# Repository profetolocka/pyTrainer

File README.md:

# pyTrainer

**pyTrainer** es un completo kit educativo diseñado para aquellos que desean introducirse en el apasionante mundo del aprendizaje de Micropython.

Ha sido creado teniendo como objetivo la sencillez y la economía, ya que puede ser replicado y construido por estudiantes o aficionados empleando técnicas caseras.

Está formado por una placa principal llamada **pyTrainer BASIC**, módulos de sensores y actuadores para interactuar con el mundo real y piezas impresas en 3D para montar las placas y crear distintas estructuras.

Este conjunto de elementos permite realizar una gran cantidad de experiencias y prácticas para aprender a programar en Micropython de una forma sencilla y divertida.<br>

## Características

### Sencillez
La placa cuenta con los elementos necesarios para practicar y aprender Micropython sin necesidad de complejas configuraciones. Enchufala y comienza a usarla!

### Potencia
Basada en la D1 Mini de Wemos, cuenta con un módulo ESP8266 capaz de realizar múltiples operaciones y conectarse a Internet a través del Wifi incluido.

### Ampliable
La pyTrainer admite la conexión de distintos módulos que amplian sus capacidades: leds RGB, pulsadores, interruptores, sensores de luz y temperatura, relés son solo algunos de ellos.
Además, el módulo D1 mini acepta distintos shields que se montan sobre la placa, como un display OLED, un sensor de temperatura o una placa de prototipos.

### Hardware y software libre
¿Quieres fabricar tu propia PyTrainer? El diseño es Open Hardware, así que puedes descargar los archivos necesarios para fabricar tu propia placa y modificarla a tu gusto.
 
## Especificaciones
* CPU: Wemos D1 mini
* Salidas digitales: Tres. Cada salida además cuenta con un led testigo.
* Entradas digitales: Tres.
* Pulsadores incorporados: Dos teclas tipo touch de uso múltiple.
* Entradas analógicas: Una con un rango de 0 a 5V.
* Otros: Zumbador activo (Buzzer).
* Ampliación: Dos conectores I2C.

[Toda la información en la Wiki](https://github.com/profetolocka/pyTrainer/wiki)

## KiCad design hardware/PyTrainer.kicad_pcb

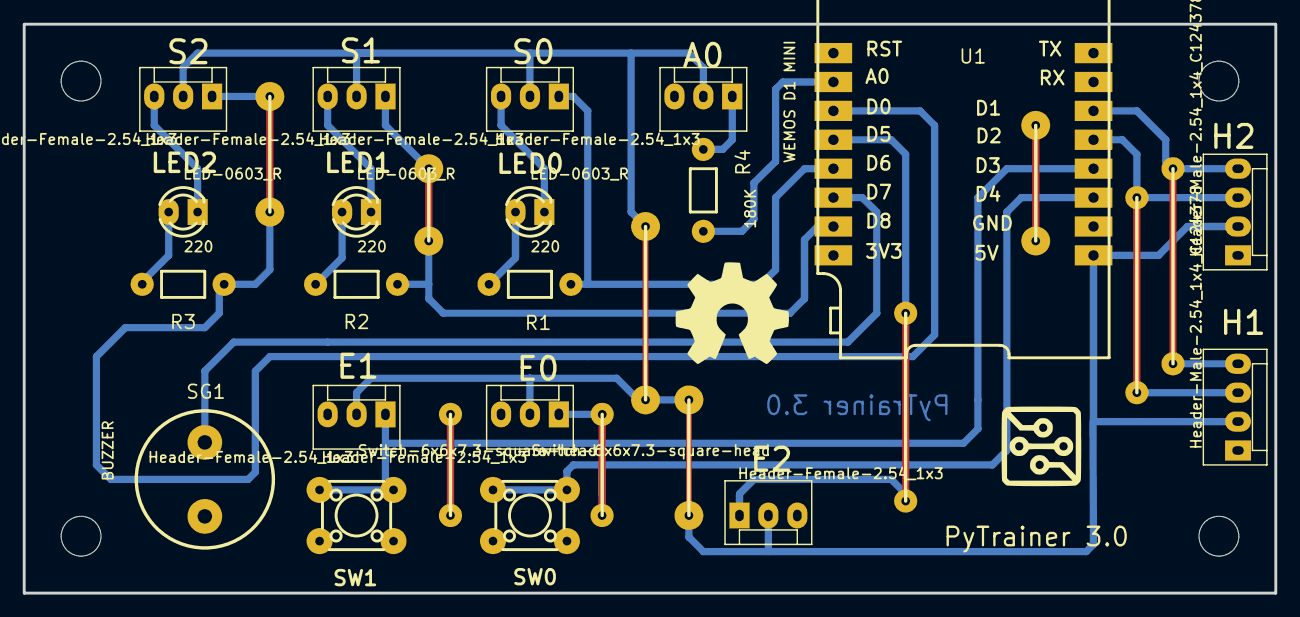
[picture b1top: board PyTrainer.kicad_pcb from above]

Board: 2 copper layers, 110.0 x 50.0 mm, 44 parts (0 on the bottom side), 16 nets.

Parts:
A0: Header-Female-2.54_1x3; MOLEX-1X3
E0, E1, E2: Header-Female-2.54_1x3; MOLEX-1X3
H1, H2: Header-Male-2.54_1x4_C124378; MOLEX-1X4
Hole_gge2783: Hole_gge2783
Hole_gge2788: Hole_gge2788
Hole_gge3649: Hole_gge3649
Hole_gge3664: Hole_gge3664
LED0, LED1, LED2: LED-0603_R; LED-TH_BD3.0-P2.54-FD
Pad_gge6454: Pad_gge6454
Pad_gge6466: Pad_gge6466
Pad_gge6478: Pad_gge6478
Pad_gge6490: Pad_gge6490
Pad_gge6502: Pad_gge6502
Pad_gge6514: Pad_gge6514
Pad_gge6526: Pad_gge6526
Pad_gge6538: Pad_gge6538
Pad_gge6550: Pad_gge6550
Pad_gge6562: Pad_gge6562
Pad_gge6574: Pad_gge6574
Pad_gge6586: Pad_gge6586
Pad_gge6598: Pad_gge6598
Pad_gge6610: Pad_gge6610
Pad_gge6622: Pad_gge6622
Pad_gge6634: Pad_gge6634
Pad_gge6655: Pad_gge6655
Pad_gge6667: Pad_gge6667
Pad_gge6679: Pad_gge6679
Pad_gge6691: Pad_gge6691
R1, R2, R3: 220; RD-3.2X1.8-1/8W
R4: 180K; RD-3.2X1.8-1/8W
S0, S1, S2: Header-Female-2.54_1x3; MOLEX-1X3
SG1: BUZZER; BUZZER-12MM-NS
SW0, SW1: Switch-6x6x7.3-square-head; SW-TH_4P-L6.0-W6.0-P4.50-LS6.5
U1: WEMOS D1 MINI

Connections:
+5V: A0.2, E0.2, E1.2, E2.2, H1.2, H2.2, S0.2, S1.2, S2.2, U1.1
A0: R4.2, U1.10
BUZZER: SG1.+, U1.14
GND: A0.3, E0.3, E1.3, E2.3, H1.1, H2.1, LED0.2, LED1.2, LED2.2, S0.3, S1.3, S2.3, SG1.-, SW0.3, SW0.4, SW1.3, SW1.4, U1.2
IN0: E1.1, SW1.1, SW1.2, U1.4
IN1: E0.1, SW0.1, SW0.2, U1.3
IN2: E2.1, U1.12
OUT0: R1.2, S0.1, U1.13
OUT1: R2.2, S1.1, U1.15
OUT2: R3.2, S2.1, U1.11
R1_1: LED0.1, R1.1
R2_1: LED1.1, R2.1
R3_1: LED2.1, R3.1
R4_1: A0.1, R4.1
SCL: H1.4, H2.4, U1.6
SDA: H1.3, H2.3, U1.5

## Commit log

2023-10-01 Carga inicial
2023-10-01 Imagen agregada
    Imagen de la pyTrainer 3 armada
2023-10-06 Add files via upload
    Agrega esquemático en PDF
2023-10-06 Create a
2023-10-06 Agrega SCH en PDF
2023-10-06 Update README.md
    Agrega otros elementos
2023-10-06 Se agregan archivos gerber
2023-10-18 Update pyTrainer.py
    Agrega sensor de distancias US
2025-07-29 Agrega hardware
2025-07-29 Agrega conectaWifi
2025-07-29 Agrega hcsr04.lib
2025-07-29 Create boot.py
    Desactiva el wifi por problemas con Mesh
2025-07-29 Update pyTrainer.py
    Agrega bip() para buzzer pasivo
2025-08-03 Update pyTrainer.py
    Incluye DHT11 (pin 5)
